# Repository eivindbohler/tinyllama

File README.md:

> **Note**  
> Version 2 of the TinyLlama is out!  
> Go here to read more: https://github.com/eivindbohler/tinyllama2

<div id="summary" align="center">
  
</div>

<br/>
<br/>

- A fully-fledged 486/Pentium-class PC in a tiny form factor
- Integrated Sound Blaster Pro-compatible audio
- Add a Raspberry Pi Zero 2 for Roland MT-32 and General MIDI music
- Open-source hardware schematics, board layout and BIOS - build your own!
- Perfect for playing DOS games!
- [YouTube feature](https://www.youtube.com/watch?v=iFZJjNTxgu8)

<br/>

## Table of Contents
- [Summary](#summary)
- [Project Goals](#project-goals)
- [History](#history)
- [Full system specs](#full-system-specs-revision-11)
- [Building](#building)
  * [Sourcing Parts](#sourcing-parts)
  * [Assembly](#assembly)
  * [Programming the BIOS](#programming-the-bios)
  * [Installing DOS](#installing-dos)
  * [Programming the CS4237B Firmware](#programming-the-cs4237b-firmware)
- [Wiki](#wiki)
- [Help](#help)
- [Roadmap](#roadmap)
- [Contributing](#contributing)
- [License](#license)
- [Contact](#contact)
- [Acknowledgements](#acknowledgments)

<br/>

## Project Goals
The goal of the TinyLlama project is:
- To create a fully x86-compatible DIY DOS computer with a sound card
- To keep the size as small as possible while keeping decent connectivity
- To keep the cost low

## History
While I regularly use and enjoy real hardware from the 80's and early 90's - this stuff is often hard to get hold of, expensive, large, heavy, unreliable and proprietary.

In 2019 this made me look into modern recreations of old hardware, and I came across [Sergey Kiselev][sergeys-projects]'s fantastic [Micro 8088][micro-8088] and various peripheral board designs.
Wanting a challenge, I modified most of these into the [PC/104][pc-104] form factor and successfully made a few prototypes:

<div>

</div>
<br />

However, being born in the early 80's and growing up playing games on 386/486-era computers, I started searching for similar projects with later hardware - and couldn't really find any. I discovered industrial boards and modules with varying degrees of ISA expandability, but these were all wildly expensive.

Then, I found the [86Duino][86duino] line of products from [DMP][dmp].  
The cheap 86Duino hardware, tailored for robotics tinkerers, seemed like a promising path. I ordered a few boards and system-on-modules and made a [prototype carrier board][hafima-image-one] with break-out ISA header pins. I intended to build an add-on sound card board, but this just proved too complex at the time, and I abandoned the project.

Fast-forward to 2021, and I saw [Rasteri's YouTube videos][rasteri-videos] detailing his experiments using different Vortex86-based industrial boards and modules, and most importantly how easy it was to utilize the powerful (and still readily available) Sound Blaster Pro-compatible Crystal CS4237B sound chip.

As fate wanted it, The Raspberry Pi Foundation had just released their Zero 2 W board, and I thought if I could put [Dale Whinham's fantastic MT32-Pi][mt32-pi] bare-metal MT-32 / General MIDI synth software on it, I would be very close to my DIY dream DOS computer.

The TinyLlama and this GitHub repo is the result.

## Full system specs (revision 1.1)
### Hardware
- **86Duino System-on-module**
  * Vortex86EX CPU running at 60-500 MHz
  * 16 KB L1 cache (can be disabled)
  * 128 KB L2 cache
  * 128 MB DDR3 RAM
  * 8 MB programmable flash ROM
- **Vortex86VGA module running off a x1 PCI-e lane**
  * Maximum resolution: 1024x768, 60 Hz
  * 4 MB SRAM
- **Crystal CS4237B all-in-one audio chip**
- **12mm PC-speaker**
- **CR1220 battery for persistent real-time clock**
- **Power and reset buttons**
- **Connectivity**
  * USB Micro-B for power (draws ~4.5W with a Pi attached, ~3W without, depending on CPU frequency)
  * 2 x USB Type-A 2.0 connectors for keyboard/mouse/storage
  * MicroSD slot for storage
  * DE-9 RS232 serial port (COM1)
  * Internal 3-pin TTL serial connector (COM2)
  * Internal 2-pin power connector for a fan (5V or 3.3V selectable)
  * 3.5mm line-out audio jack
- **MT32-Pi subsystem**
  * 40-pin connector for a Raspberry Pi Zero 2
  * 9 holes for attaching a GY-PCM5102 I²S DAC module
  * Button for toggling between MT32/General MIDI mode
  * Button for switching between audio ROM's / soundbanks
  * 4-pin I²C connector for an OLED display

### Software
- **[Custom Coreboot/SeaBIOS ROM][bios]**
- **MS-DOS / FreeDOS**

## Building
### Sourcing Parts
Full BOM (bill of materials) can be found [in the wiki][wiki-bom].
- The TinyLlama PCB
- Modern SMD and through-hole components, as seen in the BOM
- 86Duino system-on-module (SOM-128-EX)
- Vortex86VGA Mini PCI-e module
- Crystal CS4237B 100-pin TQFP. Discontinued, but readily available
- A CR1220 battery if you want persistent real-time clock
- One or more USB flash drives and/or a microSD card
- A Micro USB-B power adapter (minimum 2A)

#### For MT-32/MIDI - optional, but highly recommended
- GY-PCM5102 DAC module
- Raspberry Pi Zero 2 W with a microSD card
- An [mt32-pi compatible OLED display][mt32-pi-oled] (you don't really need it, but it's a nice addition)

### Assembly
Solder all components onto the TinyLlama PCB. As always, it's easier to start with the low-profile ones first, like resistors and capacitors.
If you're willing to spend slightly more, I recommended you let the PCB manufacturer pre-assemble most of the common components for you. Plus, some of the SMD components can be fairly tricky to solder without solder paste and a heat gun (or even better, a reflow oven).  
Take a look at the [wiki][wiki-assembly] for more in-depth assembly instructions.

### Programming the BIOS
When purchasing the SOM-128-EX module from DMP, its ROM chip comes preinstalled with an Arduino-like bootloader which is useless to us. Also, the  "crossbar" is configured for using the module with the 86Duino Zero/One boards - meaning its default pin layout is completely different from what we need for the TinyLlama.

Follow these steps to flash the ROM with the TinyLlama BIOS for the first time:
1. Find a USB flash drive, must be minimum 32 MB in size (shouldn't be a problem these days). Note that not all USB drives are bootable. Use a well-known bootable drive.
2. Unzip the `INITBIOS.ZIP` file from this GitHub repo and do a block-level transfer of the `INITBIOS.IMG` to the USB drive. Use [Balena Etcher][balena-etcher], or the command line if you know what you're doing (macOS example):
```
$ diskutil list
(Find your USB drive, eg. /dev/disk2)
$ diskutil unmountDisk /dev/disk2
$ sudo dd if=INITBIOS.IMG of=/dev/rdisk2 bs=1m
```
3. Insert the flash drive into the TinyLlama and turn it on. You should be able to enter the boot menu using F12. Select the USB drive and boot into a stripped-down FreeDOS installation. Then, to flash the ROM, type:
```
C:\>anybios w initbios.rom
```
...and reboot.
For subsequent BIOS updates, you can use the built-in BIOS updater selection available from the boot menu (press F12). This will boot into the same minimal FreeDOS installation, but from the virtual floppy drive integrated into the ROM itself.  
From there you'll only need a USB stick formatted as FAT16/FAT32 with the new BIOS file.

### Installing DOS
1. Format a microSD card or USB flash drive as a FAT32 partition with a MBR (Master Boot Record).
2. Insert it, turn on the system, press F12 to bring up the boot menu, and select the "TinyLlama BIOS updater".
3. Use `fdisk` from the command prompt to partition the SD/USB drive and set it to be `Active`.
4. Reboot and re-enter the BIOS updater boot environment. Use `format c: /s` to format the drive and copy over system files. Finally use `fdisk /mbr` to make sure the Master Boot Record is correct and the drive should be bootable.
5. Shut down the TinyLlama, eject the drive and copy over FreeDOS from another computer. I suggest putting FreeDOS in the `\FDOS` directory.
6. Set up appropriate `FDCONFIG.SYS` and `FDAUTO.BAT` files (FreeDOS equivalent versions of `CONFIG.SYS` and `AUTOEXEC.BAT`). Look at the [wiki][wiki-configuration] for examples.

### Programming the CS4237B Firmware
1. Copy the `CS4237B` and `UNISOUND` folders from this GitHub repo over to the SD/USB drive and start the system.
2. To program the firmware, run the `RESOURCE.EXE` command below and check that you get the same output:
```
C:\>cd cs4237b
C:\CS4237B>resource /f=0x120 /r=cs4237b.asm /e

Reading data from CS4237B.ASM
Length = 292    Programming EEPROM Block: 1 2    EEPROM programmed

Verifying EEPROM:
Verifying CS4237B.ASM against EEPROM . . .      Verified OKAY
```
3. Reboot the system, set a `BLASTER` environment variable and run `UNISOUND.EXE`; you should get the following output:
```
C:\>set BLASTER=A220 I7 D1 P330 T4
C:\>cd unisound
C:\UNISOUND>unisound
Universal ISA PnP Sound Card Driver for DOS v0.76f. (c) JazeFox 2019-21
-----------------------------------------------------------------------
PnP card found: [CSC7537] CS4237B
BLASTER environment var found! Loading settings...
ADD:220 WSS:534 OPL:388 IRQ:7 DMA:1/1 MPU:330/I9 CTR:120 JOY:200
Initialization done.
Crystal Mixer [VOL:85 WAV:80 FM:80 LIN:0 CD:0 MIC:0]
```
4. If everything went ok, add the `BLASTER` variable and `UNISOUND` command to your `FDAUTO.BAT`/`AUTOEXEC.BAT` file:
```
SET BLASTER=A220 I7 D1 P330 T4
C:\UNISOUND\UNISOUND.EXE /V60 /VW60 /VF60 /VL60 /VP60 /VC0 /VM0
```
5. Feel free to experiment with the different volume levels, look at the `C:\UNISOUND\UNISOUND.TXT` file for further guidance.
6. Fire up a few games to test that Adlib, SoundBlaster FM and Digital sound effects are working properly.

## Wiki
For an in-depth discussion of the various components, installation, configuration, etc, take a look at the [wiki][wiki].

## Help
This project is indended for people with a fair bit of hardware- and DOS knowledge. If you have questions or need help, please look at the [wiki][wiki] and [FAQ][wiki-faq] section first.

## Roadmap
Coming.  
In the mean time feel free to post [an issue][issues] if you have tips, suggestions or want to report an error.

## License
[GNU General Public License v3.0](LICENSE)

## Contact
[Vogons thread][vogons-thread]  
[@eivindbohler][twitter]

## Acknowledgements

Many thanks to
- [Sergey Kiselev][sergeys-projects] for a fantastic open-source suite of DIY computers, and sparking my interest in designing and building these myself.
- [Rasteri][rasteri-videos] for his cool videos about small DOS computers and the CS4237B chip.
- [The Vogons forum][vogons] for inspiration, help and support.
- [86Duino][86duino] for making a kick-ass system-on-module at an affordable price.
- [Dale Whinham / mt32-pi][mt32-pi] for making the best synth emulator software package ever.

[sergeys-projects]: http://www.malinov.com/Home/sergeys-projects
[micro-8088]: https://github.com/skiselev/micro_8088
[pc-104]: https://en.wikipedia.org/wiki/PC/104
[86duino]: https://www.86duino.com
[dmp]: https://www.dmp.com.tw
[hafima-image-one]: images/hafima2_1.jpg
[rasteri-videos]: https://www.youtube.com/user/TheRasteri/videos
[mt32-pi]: https://github.com/dwhinham/mt32-pi
[mt32-pi-oled]: https://github.com/dwhinham/mt32-pi/wiki/LCD-and-OLED-displays
[wiki]: https://github.com/eivindbohler/tinyllama/wiki
[wiki-assembly]: https://github.com/eivindbohler/tinyllama/wiki/assembly
[wiki-bom]: https://github.com/eivindbohler/tinyllama/wiki/bom
[wiki-faq]: https://github.com/eivindbohler/tinyllama/wiki/faq
[wiki-configuration]: https://github.com/eivindbohler/tinyllama/wiki/configuration
[balena-etcher]: https://www.balena.io/etcher
[issues]: https://github.com/eivindbohler/tinyllama/issues
[vogons]: https://www.vogons.org
[vogons-thread]: https://www.vogons.org/viewtopic.php?t=84880
[twitter]: https://twitter.com/eivindbohler
[bios]: https://github.com/eivindbohler/tinyllama-bios

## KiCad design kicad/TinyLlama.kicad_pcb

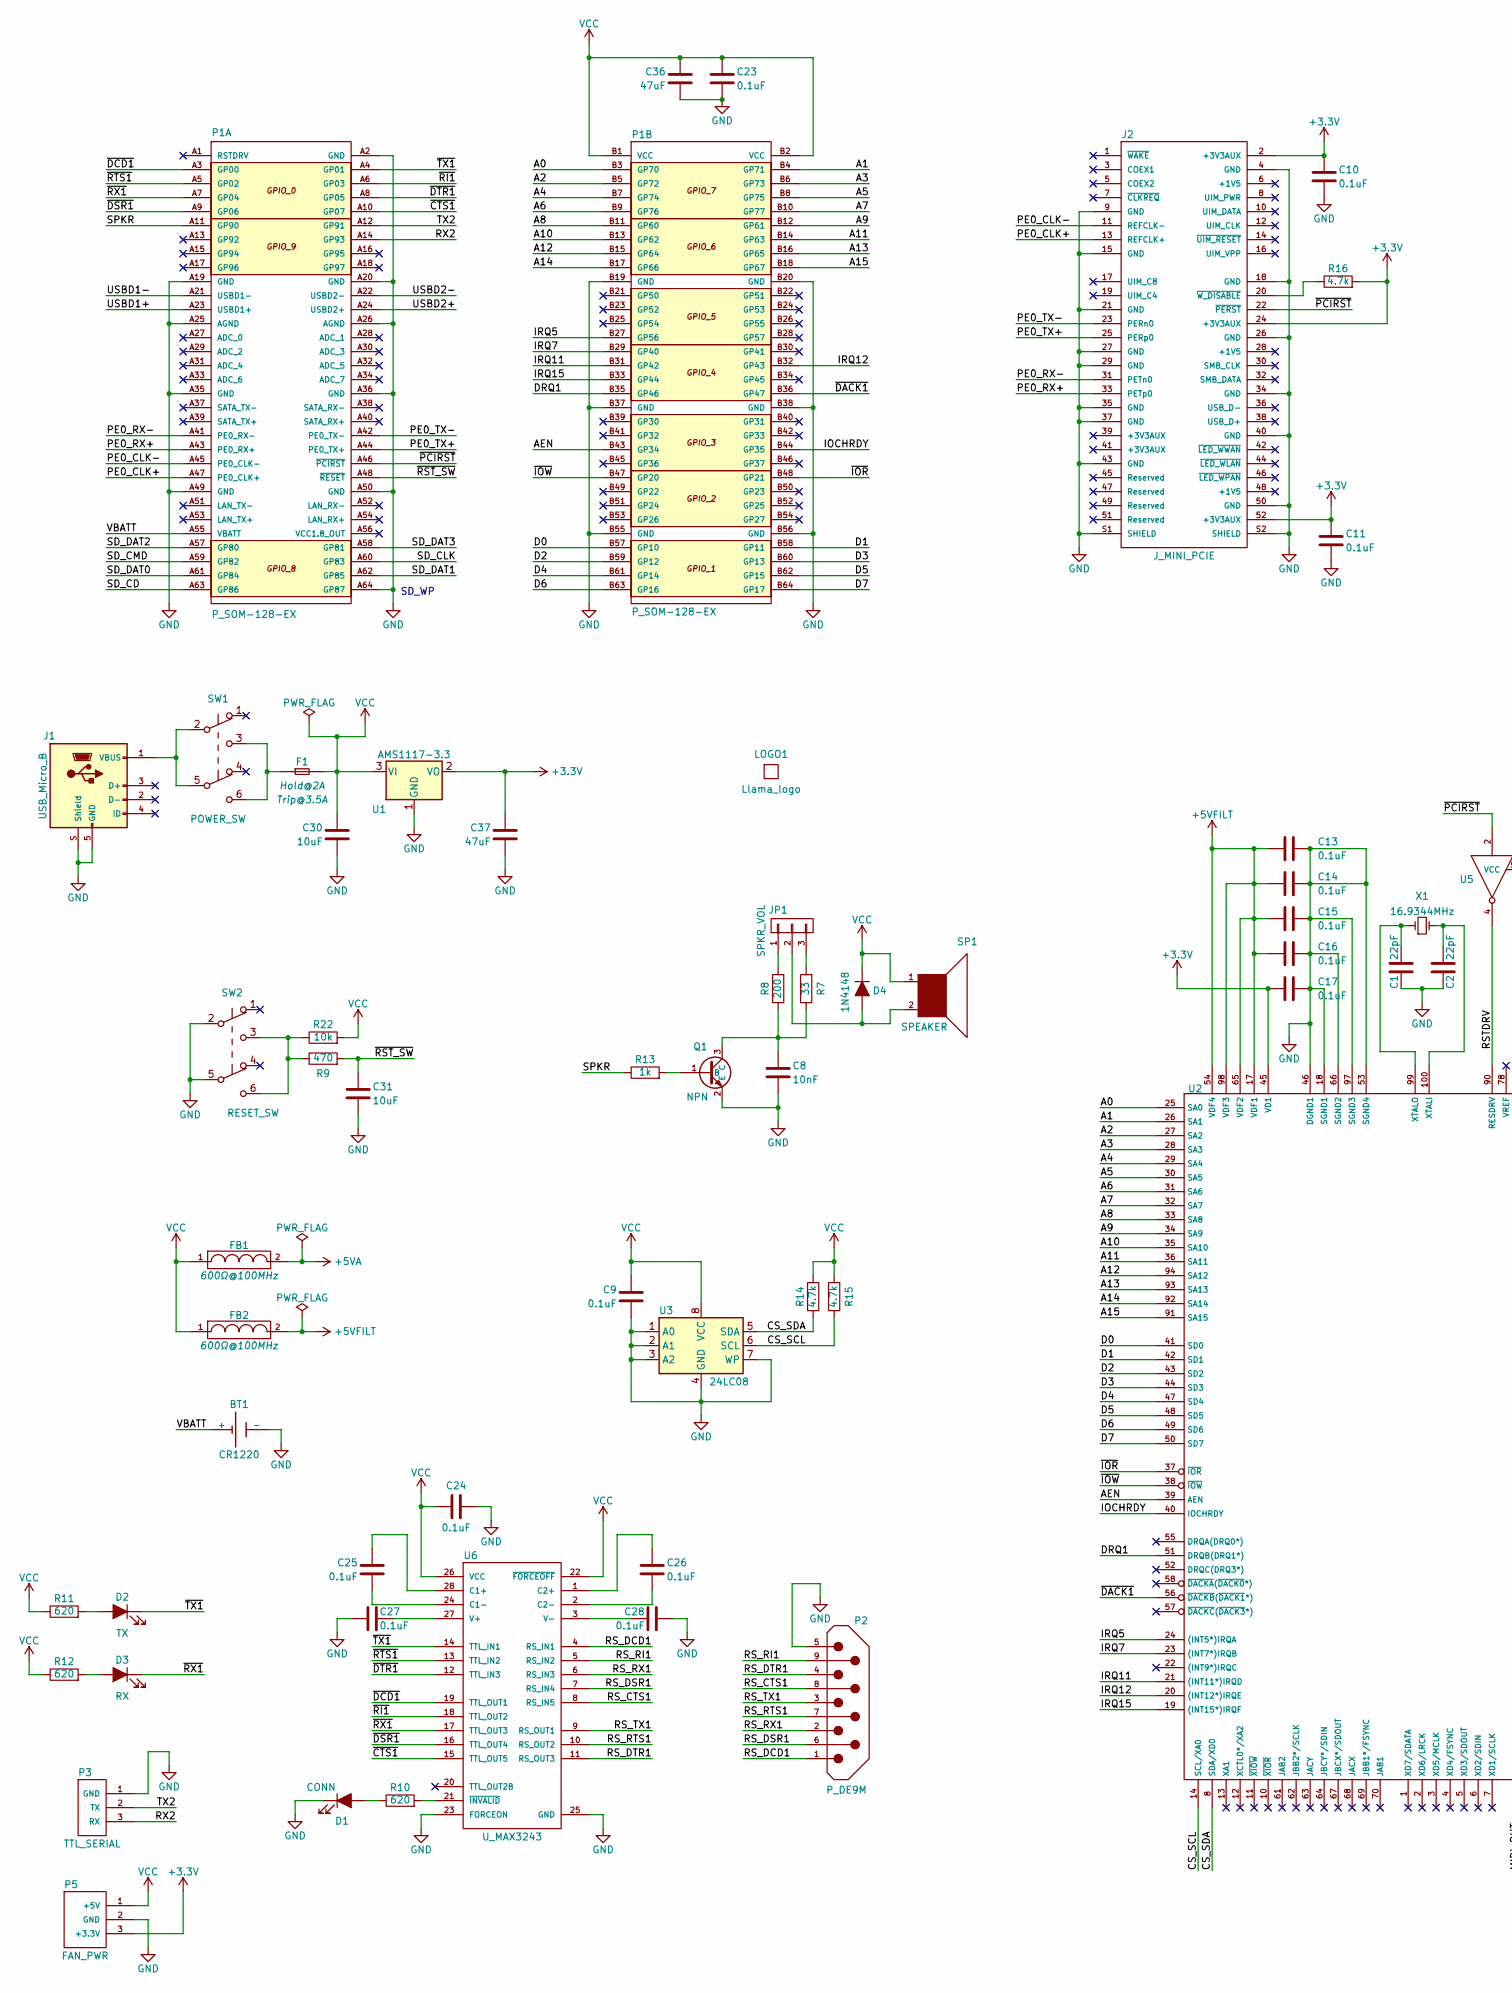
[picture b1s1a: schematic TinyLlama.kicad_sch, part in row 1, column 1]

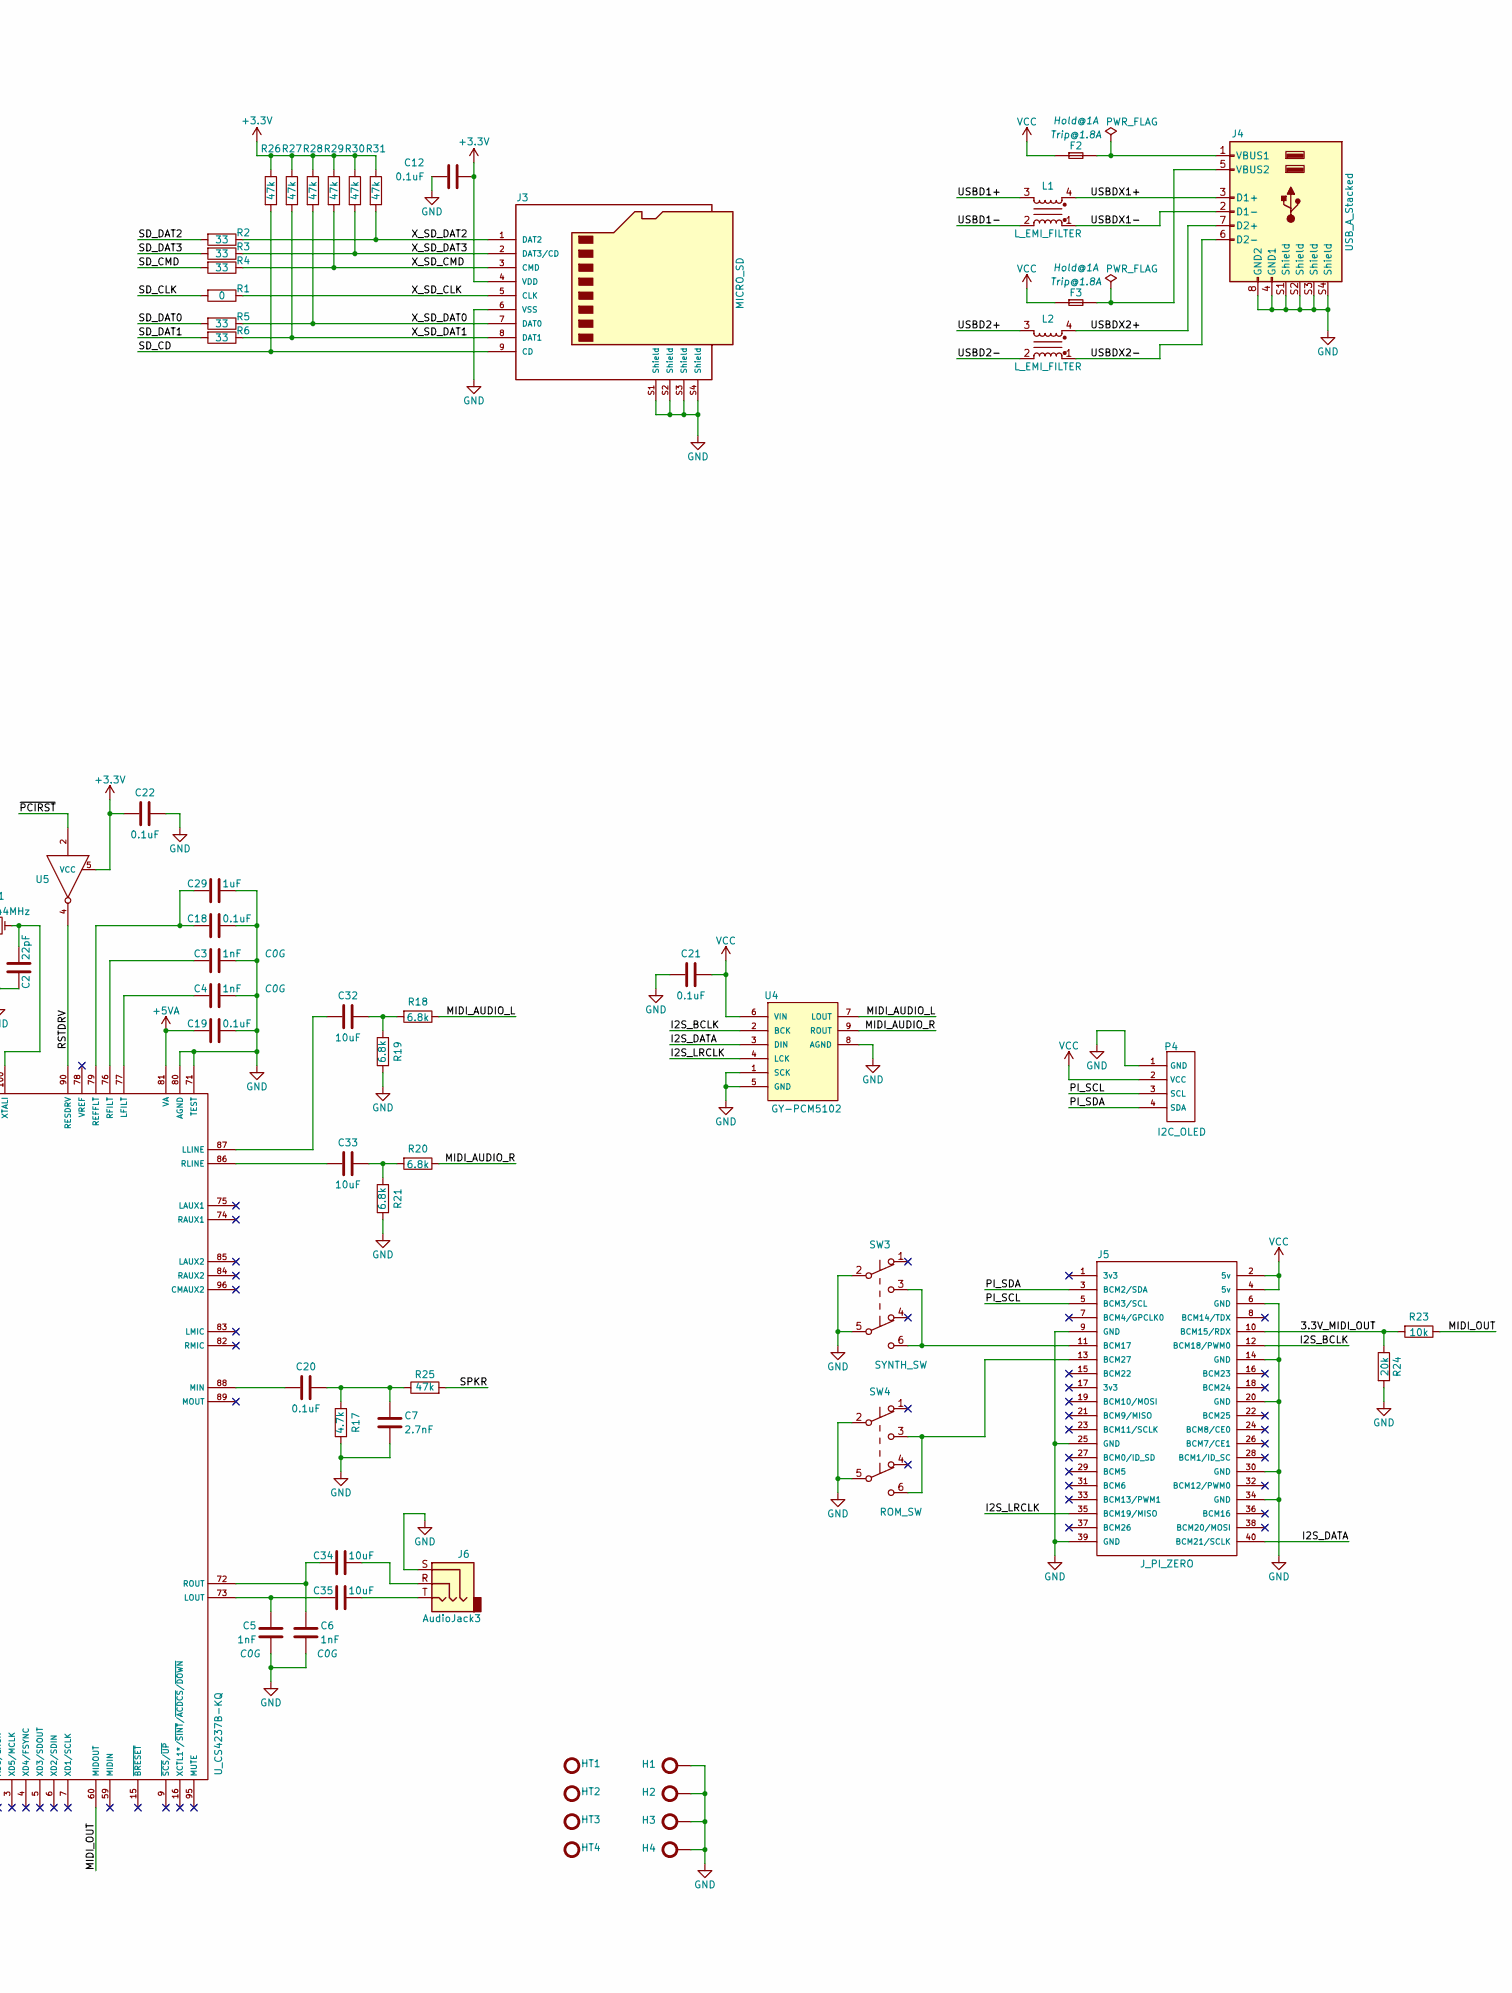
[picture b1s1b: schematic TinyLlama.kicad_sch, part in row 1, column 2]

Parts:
BT1: CR1220; MY-1220-03; LCSC C964818
C1, C2: 22pF; C_0603_1608Metric; LCSC C1653
C3, C4, C5, C6: 1nF; C_0603_1608Metric_Pad1.08x0.95mm_HandSolder; LCSC C163508
C7: 2.7nF; C_0603_1608Metric; LCSC C1609
C8: 10nF; C_0603_1608Metric; LCSC C57112
C9, C10, C11, C12, C13, C14, C15, C16, C17, C18, C19, C20, C21, C22, C23: 0.1uF; C_0603_1608Metric; LCSC C14663
C24, C25, C26, C27, C28: 0.1uF; C_0603_1608Metric_Pad1.08x0.95mm_HandSolder; LCSC C14663
C29: 1uF; C_0805_2012Metric; LCSC C28323
C30, C31, C32, C33, C34, C35: 10uF; C_0805_2012Metric; LCSC C440198
C36, C37: 47uF; C_1206_3216Metric; LCSC C96123
D1: CONN; D_0603_1608Metric
D2: TX; D_0805_2012Metric
D3: RX; D_0805_2012Metric
D4: 1N4148; D_SOD-323F; LCSC C2128
F1: F; Fuse_1206_3216Metric_Pad1.42x1.75mm_HandSolder; LCSC C151163
F2, F3: F; Fuse_0603_1608Metric_Pad1.05x0.95mm_HandSolder; LCSC C207017
FB1, FB2: FB; R_0805_2012Metric; LCSC C1017
H1, H2, H3, H4: H_HOLE; H_440_HOLE
HT1, HT2, HT3, HT4: H_HOLE_TOOLING; H_TOOLING
J1: USB_Micro_B; J_USB_MICRO_B_10118194-0001LF; LCSC C132563
J2: J_MINI_PCIE; LCSC C186111
J3: MICRO_SD; J_MicroSD_TF01A; LCSC C91145
J4: USB_A_Stacked; J_USB_A_C12049; LCSC C12049
J5: J_PI_ZERO; J_CONN_RPI; LCSC C169819
J6: AudioJack3; J_AUDIO35_C95463; LCSC C95463
JP1: SPKR_VOL; P_CONN_01X03_SQUARE
L1, L2: L_EMI_FILTER; L_EMI_FILTER_MCM2012B900GBE; LCSC C315725
LOGO1: Llama_logo; LLAMA_LOGO
P1: P_SOM-128-EX; P_CONN_SOM-128-EX
P2: P_DE9M; LCSC C75750
P3: TTL_SERIAL; P_CONN_01X03_SQUARE
P4: I2C_OLED; P_CONN_01X04_SQUARE
P5: FAN_PWR; P_CONN_01X03_SQUARE
Q1: NPN; SOT-23; LCSC C2146
R1: 0; R_0603_1608Metric; LCSC C21189
R2, R3, R4, R5, R6: 33; R_0603_1608Metric; LCSC C23140
R7: 33; R_0603_1608Metric; LCSC C23162
R8: 200; R_0603_1608Metric; LCSC C8218
R9: 470; R_0603_1608Metric; LCSC C23179
R10, R11, R12: 620; R_0603_1608Metric; LCSC C23220
R13: 1k; R_0603_1608Metric; LCSC C21190
R14, R15, R16: 4.7k; R_0603_1608Metric; LCSC C23162
R17: 4.7k; R_0603_1608Metric; LCSC C25804
R18, R19, R20, R21: 6.8k; R_0603_1608Metric; LCSC C23212
R22, R23: 10k; R_0603_1608Metric; LCSC C25804
R24: 20k; R_0603_1608Metric; LCSC C4184
R25, R26, R27, R28, R29, R30, R31: 47k; R_0603_1608Metric; LCSC C25819
SP1: SPEAKER; SP
SW1: POWER_SW; SW_ALPSALPINE_SPPH420100; LCSC C231742
SW2: RESET_SW; SW_ALPSALPINE_SPPH410200; LCSC C202363
SW3: SYNTH_SW; SW_ALPSALPINE_SPPH410200; LCSC C202363
SW4: ROM_SW; SW_ALPSALPINE_SPPH410200; LCSC C202363
U1: AMS1117-3.3; U_SOT-223-3_NOTAB; LCSC C6186
U2: U_CS4237B-KQ; U_TQFP-100_14x14mm_P0.5mm_HandSoldering
U3: 24LC08; U_SOIC-8_3.9x4.9mm_P1.27mm_HandSoldering; LCSC C5455
U4: GY-PCM5102; U_GY-PCM5102
U5: U_74LVC1G04; SOT-23-5_HandSoldering; LCSC C7827
U6: U_MAX3243; U_SSOP-28_5.3x10.2mm_P0.65mm_HandSoldering; LCSC C6853
X1: 16.9344MHz; X_Crystal_SMD_HC49-SD_HandSoldering; Mouser 815-ABLSG-16.93-D2YT

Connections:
+3.3V: C10.1, C11.1, C12.1, C17.2, C22.1, C37.1, J2.2 (+3V3AUX), J2.24 (+3V3AUX), J2.52 (+3V3AUX), J3.4 (VDD), P5.3 (+3.3V), R16.2, R26.1, R27.1, R28.1, R29.1, R30.1, R31.1, U1.2 (VO), U2.45 (VD1), U5.5 (VCC)
+5VA: C19.1, FB1.2, U2.81 (VA)
+5VFILT: C13.2, C14.2, C15.2, C16.2, FB2.2, U2.17 (VDF1), U2.54 (VDF4), U2.65 (VDF2), U2.98 (VDF3)
/3.3V_MIDI_OUT: J5.10 (BCM15/RDX), R23.2, R24.1
/A0: P1.B3 (GP70), U2.25 (SA0)
/A1: P1.B4 (GP71), U2.26 (SA1)
/A2: P1.B5 (GP72), U2.27 (SA2)
/A3: P1.B6 (GP73), U2.28 (SA3)
/A4: P1.B7 (GP74), U2.29 (SA4)
/A5: P1.B8 (GP75), U2.30 (SA5)
/A6: P1.B9 (GP76), U2.31 (SA6)
/A7: P1.B10 (GP77), U2.32 (SA7)
/A8: P1.B11 (GP60), U2.33 (SA8)
/A9: P1.B12 (GP61), U2.34 (SA9)
/A10: P1.B13 (GP62), U2.35 (SA10)
/A11: P1.B14 (GP63), U2.36 (SA11)
/A12: P1.B15 (GP64), U2.94 (SA12)
/A13: P1.B16 (GP65), U2.93 (SA13)
/A14: P1.B17 (GP66), U2.92 (SA14)
/A15: P1.B18 (GP67), U2.91 (SA15)
/AEN: P1.B43 (GP34), U2.39 (AEN)
/CS_SCL: R15.1, U2.14 (SCL/XA0), U3.6 (SCL)
/CS_SDA: R14.1, U2.8 (SDA/XD0), U3.5 (SDA)
/D0: P1.B57 (GP10), U2.41 (SD0)
/D1: P1.B58 (GP11), U2.42 (SD1)
/D2: P1.B59 (GP12), U2.43 (SD2)
/D3: P1.B60 (GP13), U2.44 (SD3)
/D4: P1.B61 (GP14), U2.47 (SD4)
/D5: P1.B62 (GP15), U2.48 (SD5)
/D6: P1.B63 (GP16), U2.49 (SD6)
/D7: P1.B64 (GP17), U2.50 (SD7)
/DRQ1: P1.B35 (GP46), U2.51 (DRQB(DRQ1*))
/I2S_BCLK: J5.12 (BCM18/PWM0), U4.2 (BCK)
/I2S_DATA: J5.40 (BCM21/SCLK), U4.3 (DIN)
/I2S_LRCLK: J5.35 (BCM19/MISO), U4.4 (LCK)
/IOCHRDY: P1.B44 (GP35), U2.40 (IOCHRDY)
/IRQ5: P1.B27 (GP56), U2.24 ((INT5*)IRQA)
/IRQ7: P1.B29 (GP40), U2.23 ((INT7*)IRQB)
/IRQ11: P1.B31 (GP42), U2.21 ((INT11*)IRQD)
/IRQ12: P1.B32 (GP43), U2.20 ((INT12*)IRQE)
/IRQ15: P1.B33 (GP44), U2.19 ((INT15*)IRQF)
/MIDI_AUDIO_L: R18.1, U4.7 (LOUT)
/MIDI_AUDIO_R: R20.1, U4.9 (ROUT)
/MIDI_OUT: R23.1, U2.60 (MIDOUT)
/PE0_CLK+: J2.13 (REFCLK+), P1.A47 (PE0_CLK+)
/PE0_CLK-: J2.11 (REFCLK-), P1.A45 (PE0_CLK-)
/PE0_RX+: J2.33 (PETp0), P1.A43 (PE0_RX+)
/PE0_RX-: J2.31 (PETn0), P1.A41 (PE0_RX-)
/PE0_TX+: J2.25 (PERp0), P1.A44 (PE0_TX+)
/PE0_TX-: J2.23 (PERn0), P1.A42 (PE0_TX-)
/PI_SCL: J5.5 (BCM3/SCL), P4.3 (SCL)
/PI_SDA: J5.3 (BCM2/SDA), P4.4 (SDA)
/RSTDRV: U2.90 (RESDRV), U5.4
/RS_CTS1: P2.8, U6.8 (RS_IN5)
/RS_DCD1: P2.1, U6.4 (RS_IN1)
/RS_DSR1: P2.6, U6.7 (RS_IN4)
/RS_DTR1: P2.4, U6.11 (RS_OUT3)
/RS_RI1: P2.9, U6.5 (RS_IN2)
/RS_RTS1: P2.7, U6.10 (RS_OUT2)
/RS_RX1: P2.2, U6.6 (RS_IN3)
/RS_TX1: P2.3, U6.9 (RS_OUT1)
/RX2: P1.A14 (GP93), P3.3 (RX)
/SD_CD: J3.9 (CD), P1.A63 (GP86), R26.2
/SD_CLK: P1.A60 (GP83), R1.2
/SD_CMD: P1.A59 (GP82), R4.2
/SD_DAT0: P1.A61 (GP84), R5.2
/SD_DAT1: P1.A62 (GP85), R6.2
/SD_DAT2: P1.A57 (GP80), R2.2
/SD_DAT3: P1.A58 (GP81), R3.2
/SPKR: P1.A11 (GP90), R13.1, R25.2
/TX2: P1.A12 (GP91), P3.2 (TX)
/USBD1+: L1.3, P1.A23 (USBD1+)
/USBD1-: L1.2, P1.A21 (USBD1-)
/USBD2+: L2.3, P1.A24 (USBD2+)
/USBD2-: L2.2, P1.A22 (USBD2-)
/USBDX1+: J4.3 (D1+), L1.4
/USBDX1-: J4.2 (D1-), L1.1
/USBDX2+: J4.7 (D2+), L2.4
/USBDX2-: J4.6 (D2-), L2.1
/VBATT: BT1.1 (+), P1.A55 (VBATT)
/X_SD_CLK: J3.5 (CLK), R1.1
/X_SD_CMD: J3.3 (CMD), R4.1, R29.2
/X_SD_DAT0: J3.7 (DAT0), R5.1, R28.2
/X_SD_DAT1: J3.8 (DAT1), R6.1, R27.2
/X_SD_DAT2: J3.1 (DAT2), R2.1, R31.2
/X_SD_DAT3: J3.2 (DAT3/CD), R3.1, R30.2
/~CTS1: P1.A10 (GP07), U6.15 (TTL_OUT5)
/~DACK1: P1.B36 (GP47), U2.56 (~DACKB(~DACK1*))
/~DCD1: P1.A3 (GP00), U6.19 (TTL_OUT1)
/~DSR1: P1.A9 (GP06), U6.16 (TTL_OUT4)
/~DTR1: P1.A8 (GP05), U6.12 (TTL_IN3)
/~IOR: P1.B48 (GP21), U2.37 (~IOR)
/~IOW: P1.B47 (GP20), U2.38 (~IOW)
/~PCIRST: J2.22 (~PERST), P1.A46 (~PCIRST), U5.2
/~RI1: P1.A6 (GP03), U6.18 (TTL_OUT2)
/~RST_SW: C31.1, P1.A48 (~RESET), R9.2
/~RTS1: P1.A5 (GP02), U6.13 (TTL_IN2)
/~RX1: D3.1 (K), P1.A7 (GP04), U6.17 (TTL_OUT3)
/~TX1: D2.1 (K), P1.A4 (GP01), U6.14 (TTL_IN1)
GND: BT1.2 (-), C1.1, C2.1, C3.2, C4.2, C5.2, C6.2, C7.2, C8.2, C9.2, C10.2, C11.2, C12.2, C13.1, C14.1, C15.1, C16.1, C17.1, C18.2, C19.2, C21.1, C22.2, C23.2, C24.2, C27.2, C28.1, C29.2, C30.2, C31.2, C36.2, C37.2, D1.1 (K), H1.1, H2.1, H3.1, H4.1, J1.5 (GND), J1.S (Shield), J2.4 (GND), J2.9 (GND), J2.15 (GND), J2.18 (GND), J2.21 (GND), J2.26 (GND), J2.27 (GND), J2.29 (GND), J2.34 (GND), J2.35 (GND), J2.37 (GND), J2.40 (GND), J2.43 (GND), J2.50 (GND), J2.S1 (SHIELD), J2.S2 (SHIELD), J3.6 (VSS), J3.S1 (Shield), J3.S2 (Shield), J3.S3 (Shield), J3.S4 (Shield), J4.4 (GND1), J4.8 (GND2), J4.S1 (Shield), J4.S2 (Shield), J4.S3 (Shield), J4.S4 (Shield), J5.6 (GND), J5.9 (GND), J5.14 (GND), J5.20 (GND), J5.25 (GND), J5.30 (GND), J5.34 (GND), J5.39 (GND), J6.S, P1.A2 (GND), P1.A19 (GND), P1.A20 (GND), P1.A25 (AGND), P1.A26 (AGND), P1.A35 (GND), P1.A36 (GND), P1.A49 (GND), P1.A50 (GND), P1.A64 (GP87), P1.B19 (GND), P1.B20 (GND), P1.B37 (GND), P1.B38 (GND), P1.B55 (GND), P1.B56 (GND), P2.5, P2.10 (GND), P2.11 (GND), P3.1 (GND), P4.1 (GND), P5.2 (GND), Q1.2 (E), R17.1, R19.1, R21.1, R24.2, SW2.2 (B), SW2.5 (B), SW3.2 (B), SW3.5 (B), SW4.2 (B), SW4.5 (B), U1.1 (GND), U2.18 (SGND1), U2.46 (DGND1), U2.53 (SGND4), U2.66 (SGND2), U2.71 (TEST), U2.80 (AGND), U2.97 (SGND3), U3.1 (A0), U3.2 (A1), U3.3 (A2), U3.4 (GND), U3.7 (WP), U4.1 (SCK), U4.5 (GND), U4.8 (AGND), U5.3 (GND), U6.23 (FORCEON), U6.25 (GND)
unnamed: C1.2, U2.99 (XTALO), X1.1
unnamed: C2.2, U2.100 (XTALI), X1.2
unnamed: C3.1, U2.76 (RFILT)
unnamed: C4.1, U2.77 (LFILT)
unnamed: C8.1, Q1.3 (C), R7.1, R8.1
unnamed: C18.1, C29.1, U2.79 (REFFLT)
unnamed: C20.1, U2.88 (MIN)
unnamed: C7.1, C20.2, R17.2, R25.1
unnamed: C25.1, U6.28 (C1+)
unnamed: C25.2, U6.24 (C1-)
unnamed: C26.1, U6.1 (C2+)
unnamed: C26.2, U6.2 (C2-)
unnamed: C27.1, U6.27 (V+)
unnamed: C28.2, U6.3 (V-)
unnamed: C32.1, U2.87 (LLINE)
unnamed: C32.2, R18.2, R19.2
unnamed: C33.1, U2.86 (RLINE)
unnamed: C33.2, R20.2, R21.2
unnamed: C6.1, C34.1, U2.72 (ROUT)
unnamed: C34.2, J6.R
unnamed: C5.1, C35.1, U2.73 (LOUT)
unnamed: C35.2, J6.T
unnamed: D1.2 (A), R10.1
unnamed: D2.2 (A), R11.2
unnamed: D3.2 (A), R12.2
unnamed: D4.2 (A), JP1.2, SP1.2
unnamed: F1.1, SW1.3 (C), SW1.6 (C)
unnamed: F2.2, J4.1 (VBUS1)
unnamed: F3.2, J4.5 (VBUS2)
unnamed: J1.1 (VBUS), SW1.2 (B), SW1.5 (B)
unnamed: J2.20 (~W_DISABLE), R16.1
unnamed: J5.11 (BCM17), SW3.3 (C), SW3.6 (C)
unnamed: J5.13 (BCM27), SW4.3 (C), SW4.6 (C)
unnamed: JP1.1, R8.2
unnamed: JP1.3, R7.2
unnamed: Q1.1 (B), R13.2
unnamed: R10.2, U6.21 (~INVALID)
unnamed: R9.1, R22.1, SW2.3 (C), SW2.6 (C)
VCC: C9.1, C21.2, C23.1, C24.1, C30.1, C36.1, D4.1 (K), F1.2, F2.1, F3.1, FB1.1, FB2.1, J5.2 (5v), J5.4 (5v), P1.B1 (VCC), P1.B2 (VCC), P4.2 (VCC), P5.1 (+5V), R11.1, R12.1, R14.2, R15.2, R22.2, SP1.1, U1.3 (VI), U3.8 (VCC), U4.6 (VIN), U6.22 (~FORCEOFF), U6.26 (VCC)

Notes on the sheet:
SD_WP

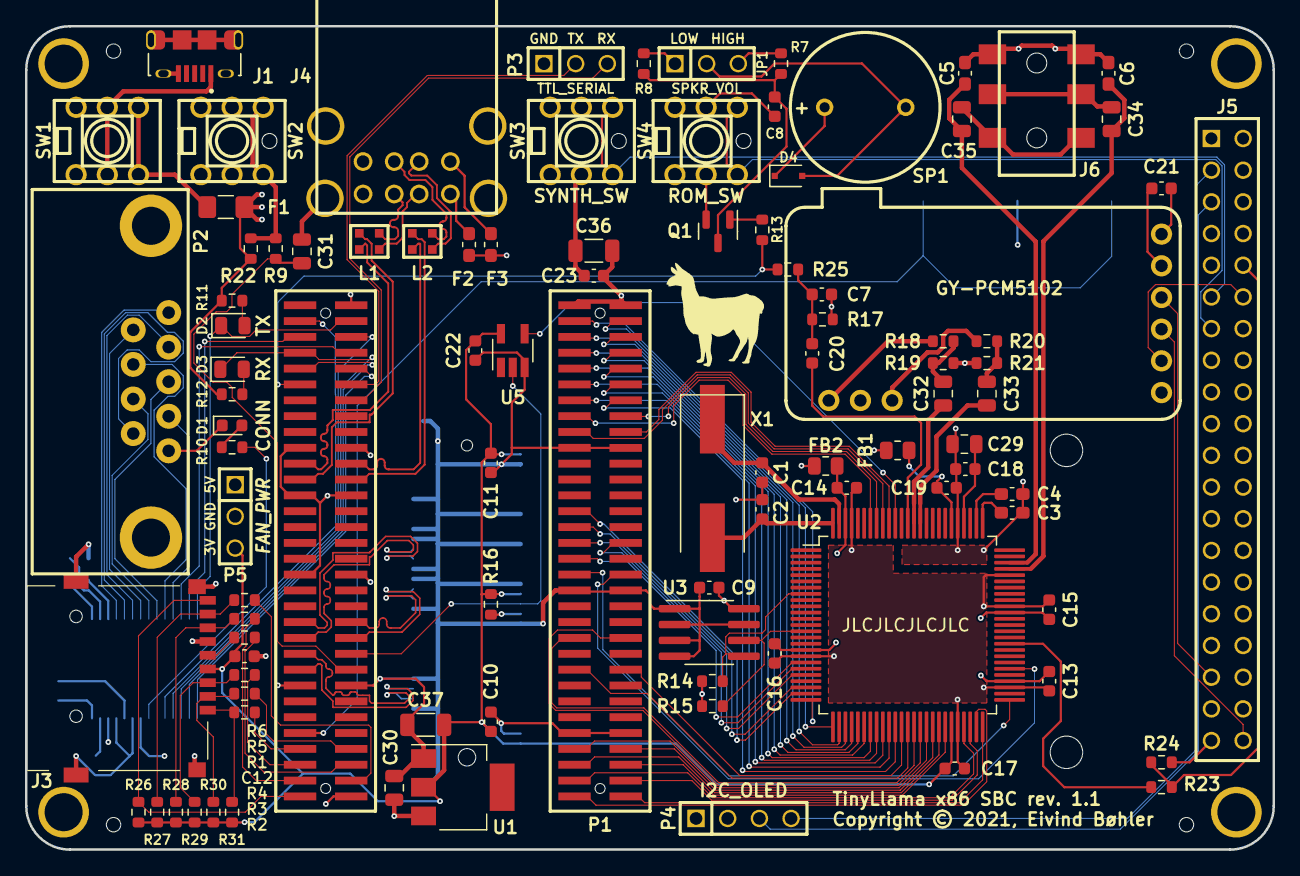
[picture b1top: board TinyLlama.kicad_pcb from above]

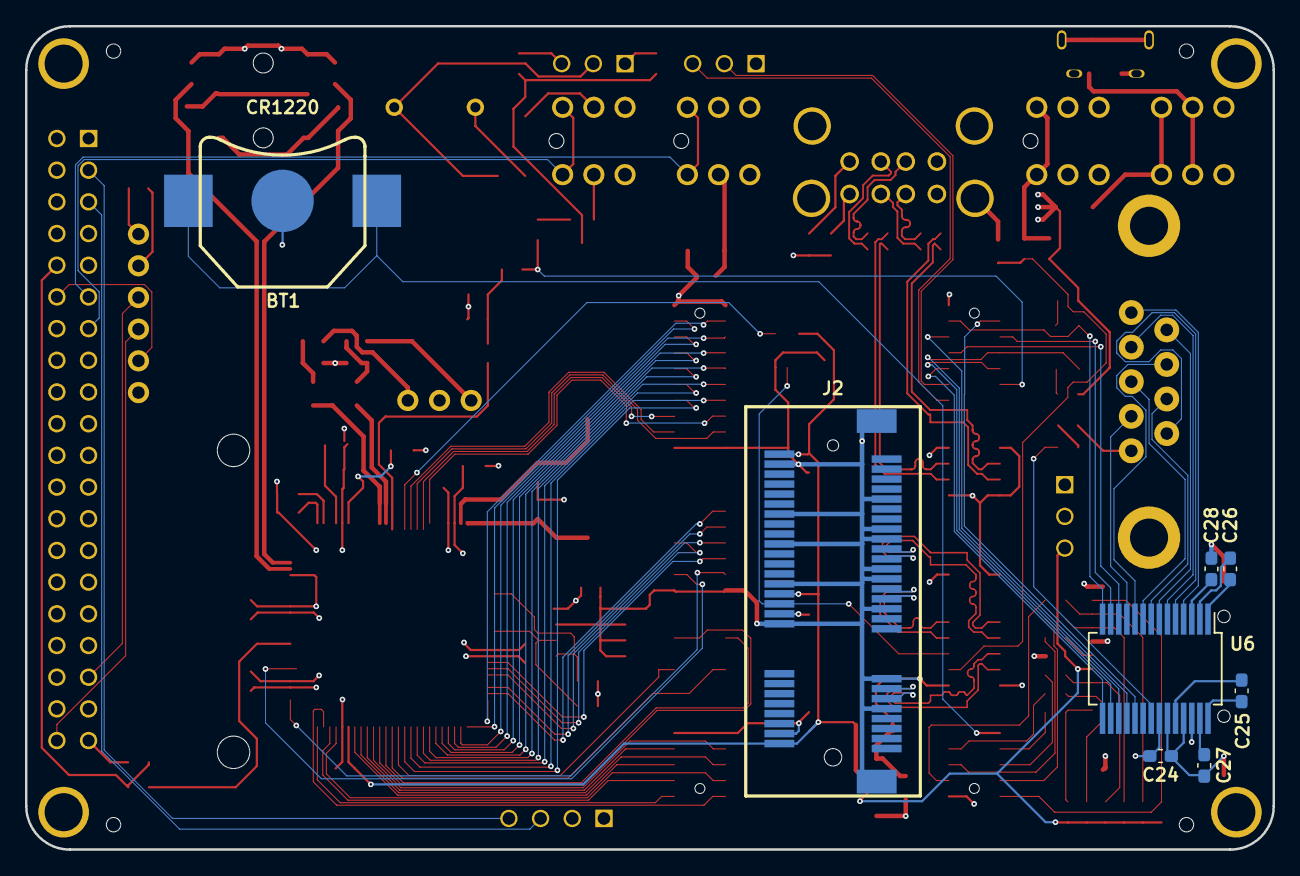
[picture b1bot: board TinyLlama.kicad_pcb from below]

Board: 4 copper layers, 100.0 x 66.0 mm, 114 parts (8 on the bottom side), 139 nets.

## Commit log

2022-10-31 Improved README text
2022-10-31 Added example 3D printed case files
2022-11-06 Add USB bulk cap issue to errata
2022-11-11 Add RS232 FORCEON issue to errata
2022-11-13 Update INITBIOS to rev1.1-20221113-184625
2022-11-13 Update INITBIOS to rev1.1-20221113-213951
2022-11-14 Update INITBIOS to rev1.1-20221115-002119
2022-11-29 Add clarification about IC in errata
2022-11-30 Update INITBIOS to rev1.1-20221201-003413
2023-03-08 Add version 2 notification to README

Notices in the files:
kicad/TinyLlama.kicad_pcb:
Copyright © 2021, Eivind Bøhler
